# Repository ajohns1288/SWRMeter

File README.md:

# SWRMeter
PCB files, 3D printing files, and Arduino program to replace the traditional crossed needles SWR meter.

This project was originally done to replace the crossed needle meter on my LDG AT-11MP Tuner, as the meter was broken and replacement parts no longer available.

# To Calibrate
1: Compile with _CALIBRATE_SHOW_COUNTS == 1

2: Attach meter to DUT, transmit into dummy load using FM at 5W and record number on display.

3: Repeat for power values listed in LUT_FWD[] (you can extrapolate if your transmitter only goes so high)

4: Transmit backwards (INTO antenna port with dummy load on TX port) and record number for Ref Pwr. (May want to limit power and extrapolate)

5: Enter recorded values into LUT_FWD[] and LUT_REF[], set _CALIBRATE_SHOW_COUNTS == 0, and compile.

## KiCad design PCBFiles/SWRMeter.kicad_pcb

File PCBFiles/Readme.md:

# PCB Files
This should be everything needed to get a PCB fabbed.

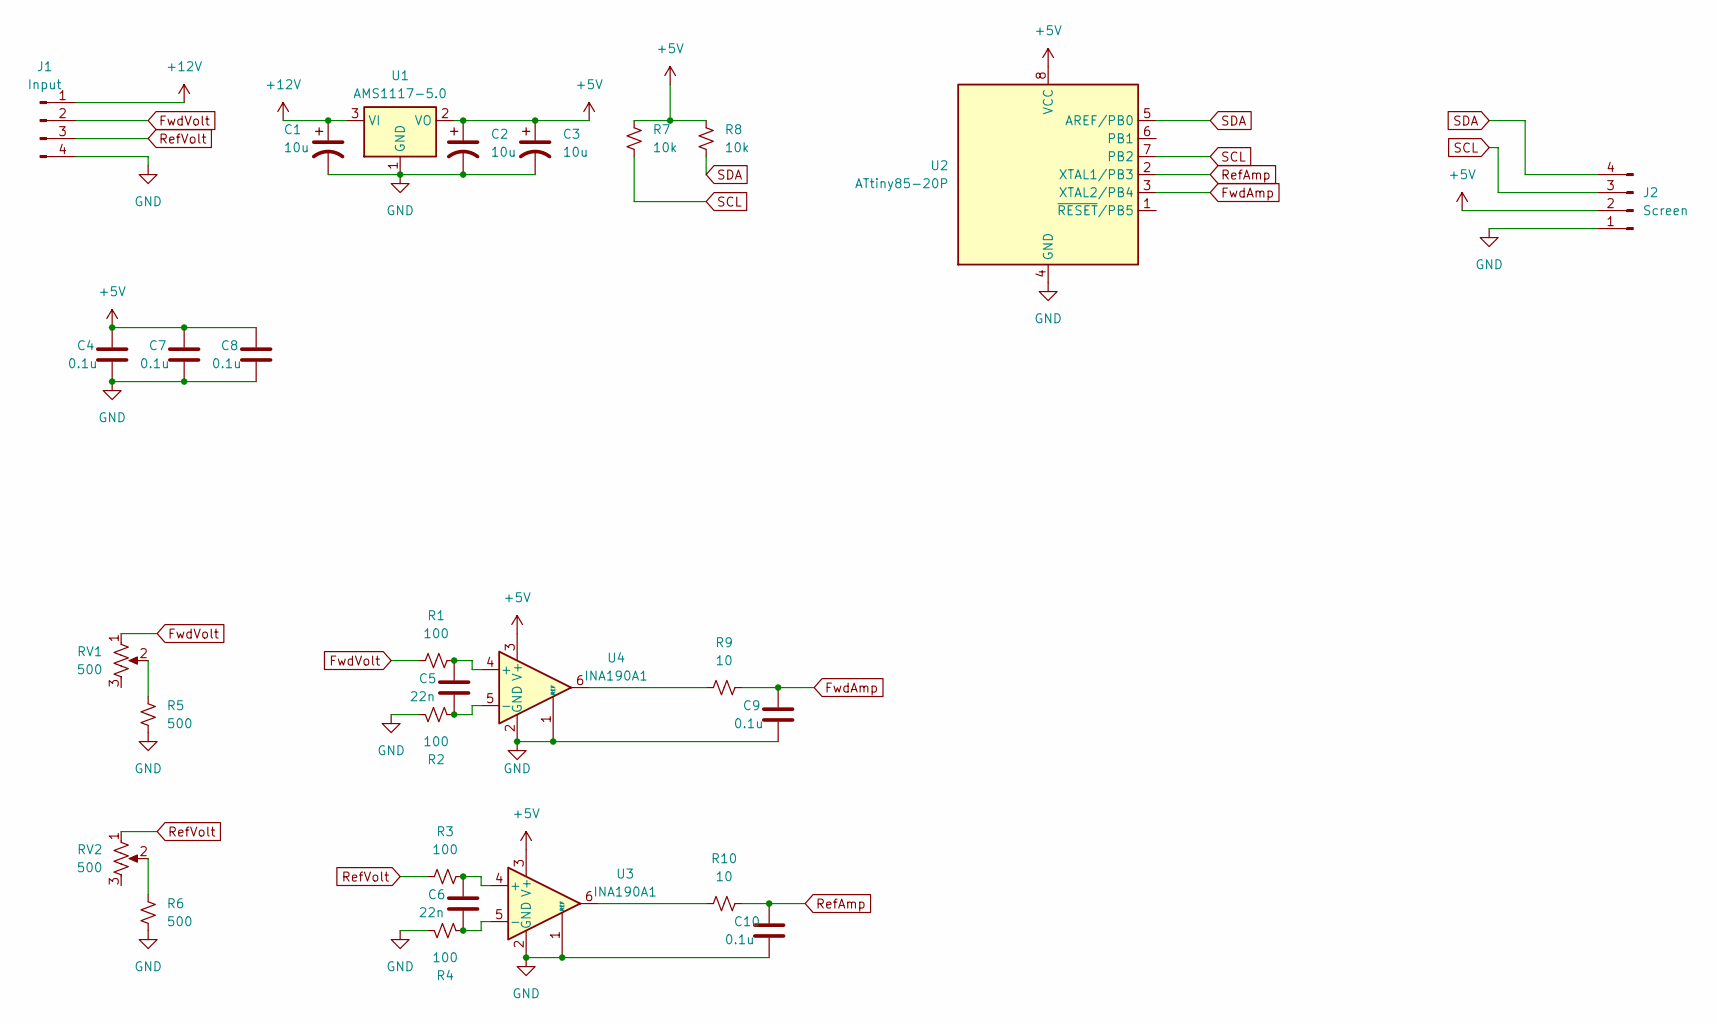
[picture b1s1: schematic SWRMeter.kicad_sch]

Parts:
C1, C2, C3: 10u; CP_EIA-3216-12_Kemet-S
C4, C7, C8, C9, C10: 0.1u; C_0603_1608Metric
C5, C6: 22n; C_0603_1608Metric
J1: Input; PinHeader_1x04_P2.54mm_Vertical
J2: Screen; PinHeader_1x04_P2.54mm_Vertical
R1, R2, R3, R4: 100; R_0603_1608Metric
R5, R6: 500; R_0603_1608Metric
R7, R8: 10k; R_0603_1608Metric
R9, R10: 10; R_0603_1608Metric
RV1, RV2: 500; Potentiometer_Bourns_3314J_Vertical
U1: AMS1117-5.0; SOT-223-3_TabPin2
U2: ATtiny85-20P; DIP-8_W7.62mm
U3, U4: INA190A1; SOT-363_SC-70-6_Handsoldering

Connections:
+5V: C2.1, C3.1, C4.2, C7.2, C8.2, J2.2, R7.1, R8.1, U1.2 (VO), U2.8 (VCC), U3.3 (V+), U4.3 (V+)
+12V: C1.1, J1.1, U1.3 (VI)
FwdAmp: C9.2, R9.2, U2.3 (XTAL2/PB4)
FwdVolt: J1.2, R1.1, RV1.1
GND: C1.2, C2.2, C3.2, C4.1, C7.1, C8.1, C9.1, C10.1, J1.4, J2.1, R2.1, R4.1, R5.2, R6.2, U1.1 (GND), U2.4 (GND), U3.1 (REF), U3.2 (GND), U4.1 (REF), U4.2 (GND)
unnamed: R5.1, RV1.2
unnamed: R6.1, RV2.2
unnamed: R9.1, U4.6
unnamed: R10.1, U3.6
unnamed: C6.2, R3.2, U3.4 (+)
unnamed: C6.1, R4.2, U3.5 (-)
unnamed: C5.2, R1.2, U4.4 (+)
unnamed: C5.1, R2.2, U4.5 (-)
RefAmp: C10.2, R10.2, U2.2 (XTAL1/PB3)
RefVolt: J1.3, R3.1, RV2.1
SCL: J2.3, R7.2, U2.7 (PB2)
SDA: J2.4, R8.2, U2.5 (AREF/PB0)

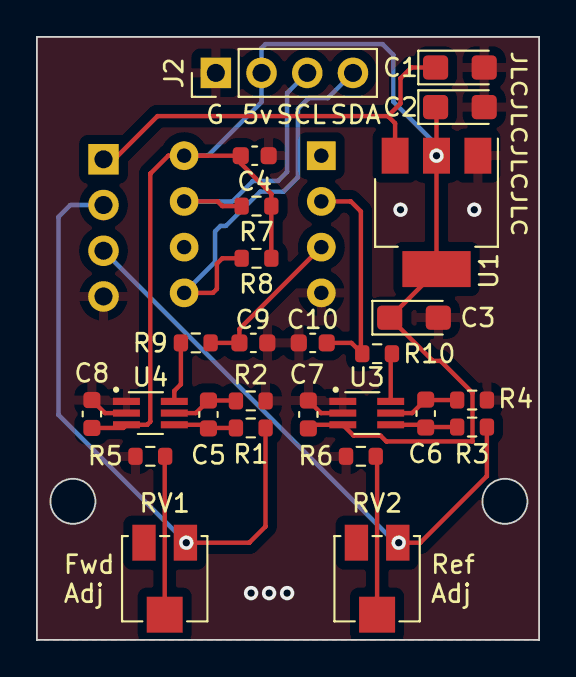
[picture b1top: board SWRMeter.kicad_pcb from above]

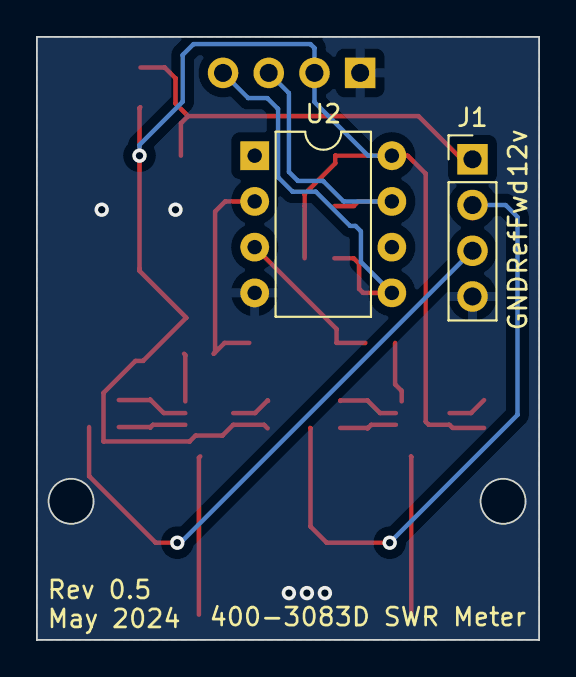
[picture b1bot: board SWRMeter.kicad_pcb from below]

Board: 2 copper layers, 27.9 x 33.5 mm, 28 parts (2 on the bottom side), 17 nets.
